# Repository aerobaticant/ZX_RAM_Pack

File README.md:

# ZX RAM Pack
This is my design for a RAM pack for the Sinclair ZX81 computer.
<br>It uses a 62256 SRAM IC to give 32KiB of RAM available to BASIC.

<picture></picture>

## PLD
A 16V8 PLD is used to do the address decoding.

RAM is enabled when A13, A14 or A15 are high ($2000-$FFFF)
<br>RAM area $4000-$7FFF is shadowed at $C000-$FFFF

RAM is read during MREQ or RFSH to allow Hi Res Graphics

ROM shadow is disabled when A15 is high ($8000-$BFFF)
<br>Note: ZX80 has no ROMCS signal so ROM shadow can't be disabled
<br>This means the ZX80 can only be given 16K

ROM is also disabled in address $0004 following reset to allow auto detection
<br>Pull-ups on the data bus generate LD BC,$FFFF instead of LD BC,$7FFF for RAM-CHECK

## Schematic
The Schematic and PCB were created in KiCAD

## STLs
I have also created a 3D printable enclosure based on the design of the original ZX80's 3KB RAM pack.
<br>You may have to rotate the parts to suit your 3D printer.

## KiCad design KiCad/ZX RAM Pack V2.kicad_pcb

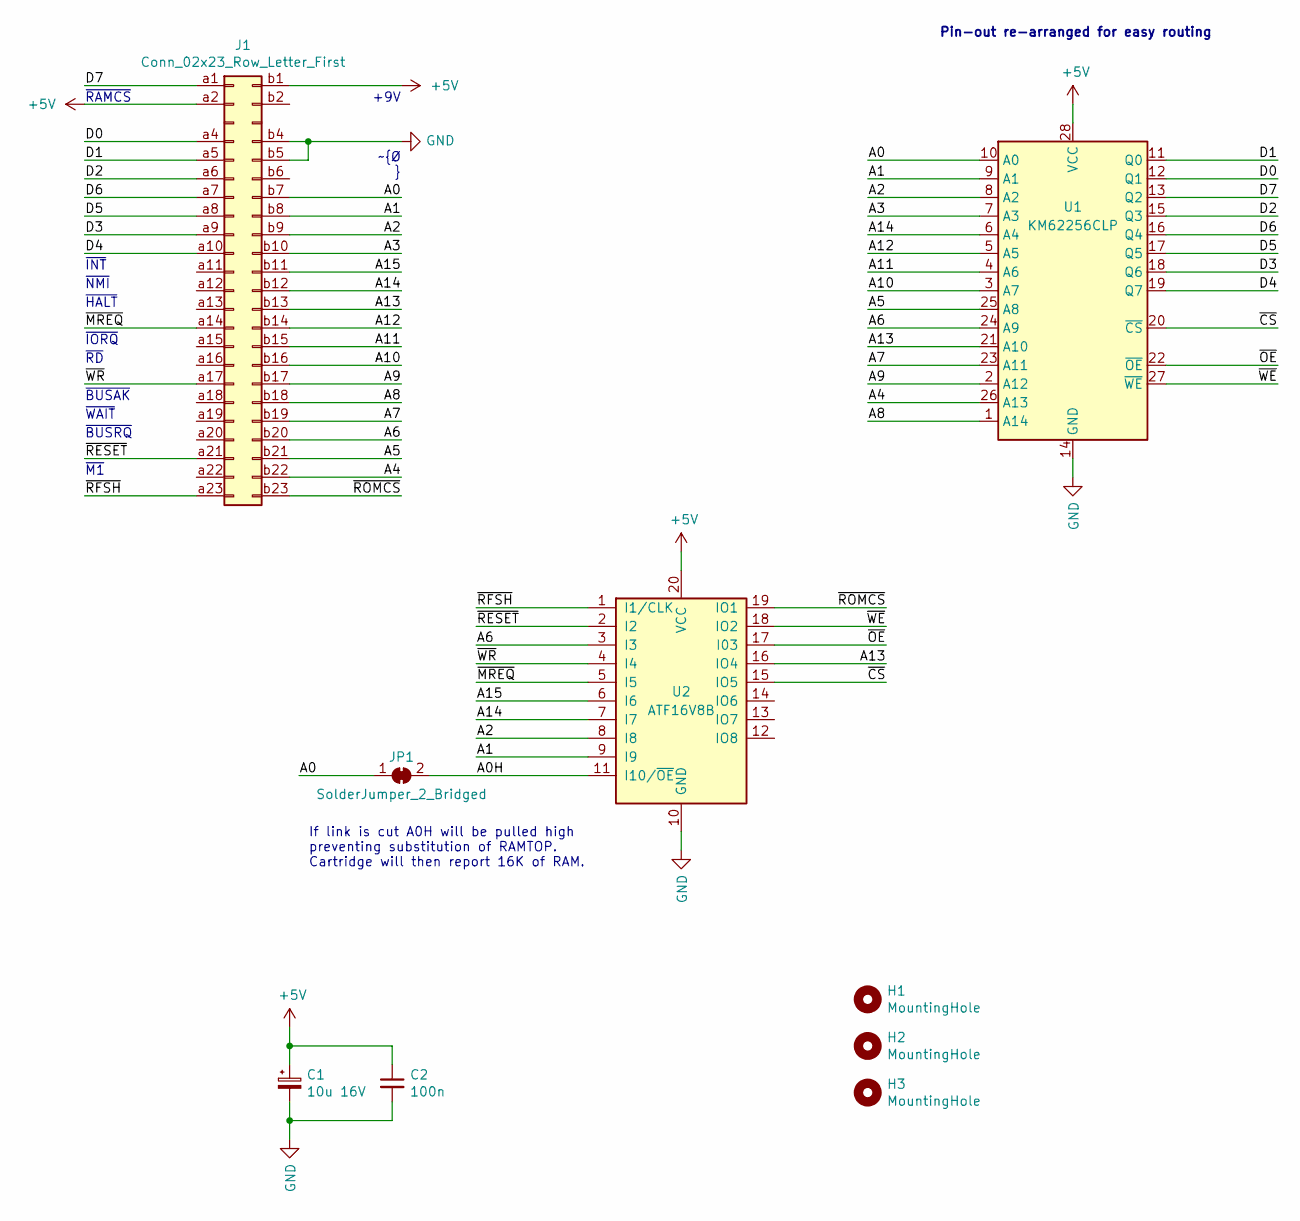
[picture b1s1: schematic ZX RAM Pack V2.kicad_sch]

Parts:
C1: 10u 16V; CP_Radial_D5.0mm_P2.50mm
C2: 100n; C_Disc_D4.3mm_W1.9mm_P5.00mm
H1, H2, H3: MountingHole; MountingHole_3.2mm_M3
J1: Conn_02x23_Row_Letter_First; Connector_ZX80_ZX80_Card_Edge_2x24
JP1: SolderJumper_2_Bridged; SolderJumper-2_P1.3mm_Bridged_RoundedPad1.0x1.5mm
U1: KM62256CLP; DIP-28_W15.24mm_Socket_LongPads
U2: ATF16V8B; DIP-20_W7.62mm_Socket_LongPads

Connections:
+5V: C1.1, C2.1, J1.a2, J1.b1, U1.28 (VCC), U2.20 (VCC)
/A0: J1.b7, JP1.1 (A), U1.10 (A0)
/A0H: JP1.2 (B), U2.11 (I10/~OE)
/A1: J1.b8, U1.9 (A1), U2.9 (I9)
/A2: J1.b9, U1.8 (A2), U2.8 (I8)
/A3: J1.b10, U1.7 (A3)
/A4: J1.b22, U1.26 (A13)
/A5: J1.b21, U1.25 (A8)
/A6: J1.b20, U1.24 (A9), U2.3 (I3)
/A7: J1.b19, U1.23 (A11)
/A8: J1.b18, U1.1 (A14)
/A9: J1.b17, U1.2 (A12)
/A10: J1.b16, U1.3 (A7)
/A11: J1.b15, U1.4 (A6)
/A12: J1.b14, U1.5 (A5)
/A13: J1.b13, U1.21 (A10), U2.16 (IO4)
/A14: J1.b12, U1.6 (A4), U2.7 (I7)
/A15: J1.b11, U2.6 (I6)
/D0: J1.a4, U1.12 (Q1)
/D1: J1.a5, U1.11 (Q0)
/D2: J1.a6, U1.15 (Q3)
/D3: J1.a9, U1.18 (Q6)
/D4: J1.a10, U1.19 (Q7)
/D5: J1.a8, U1.17 (Q5)
/D6: J1.a7, U1.16 (Q4)
/D7: J1.a1, U1.13 (Q2)
/~CS: U1.20 (~CS), U2.15 (IO5)
/~MREQ: J1.a14, U2.5 (I5)
/~OE: U1.22 (~OE), U2.17 (I03)
/~RESET: J1.a21, U2.2 (I2)
/~RFSH: J1.a23, U2.1 (I1/CLK)
/~ROMCS: J1.b23, U2.19 (IO1)
/~WE: U1.27 (~WE), U2.18 (IO2)
/~WR: J1.a17, U2.4 (I4)
GND: C1.2, C2.2, J1.b4, J1.b5, U1.14 (GND), U2.10 (GND)

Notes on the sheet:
+9V
~{IORQ}
~{INT}
If link is cut A0H will be pulled high preventing substitution of RAMTOP. Cartridge will then report 16K of RAM.
~{BUSRQ}
~{NMI}
Pin-out re-arranged for easy routing
~{RAMCS}
~{WAIT}
~{M1}
~{Ø }
~{HALT}
~{BUSAK}
~{RD}

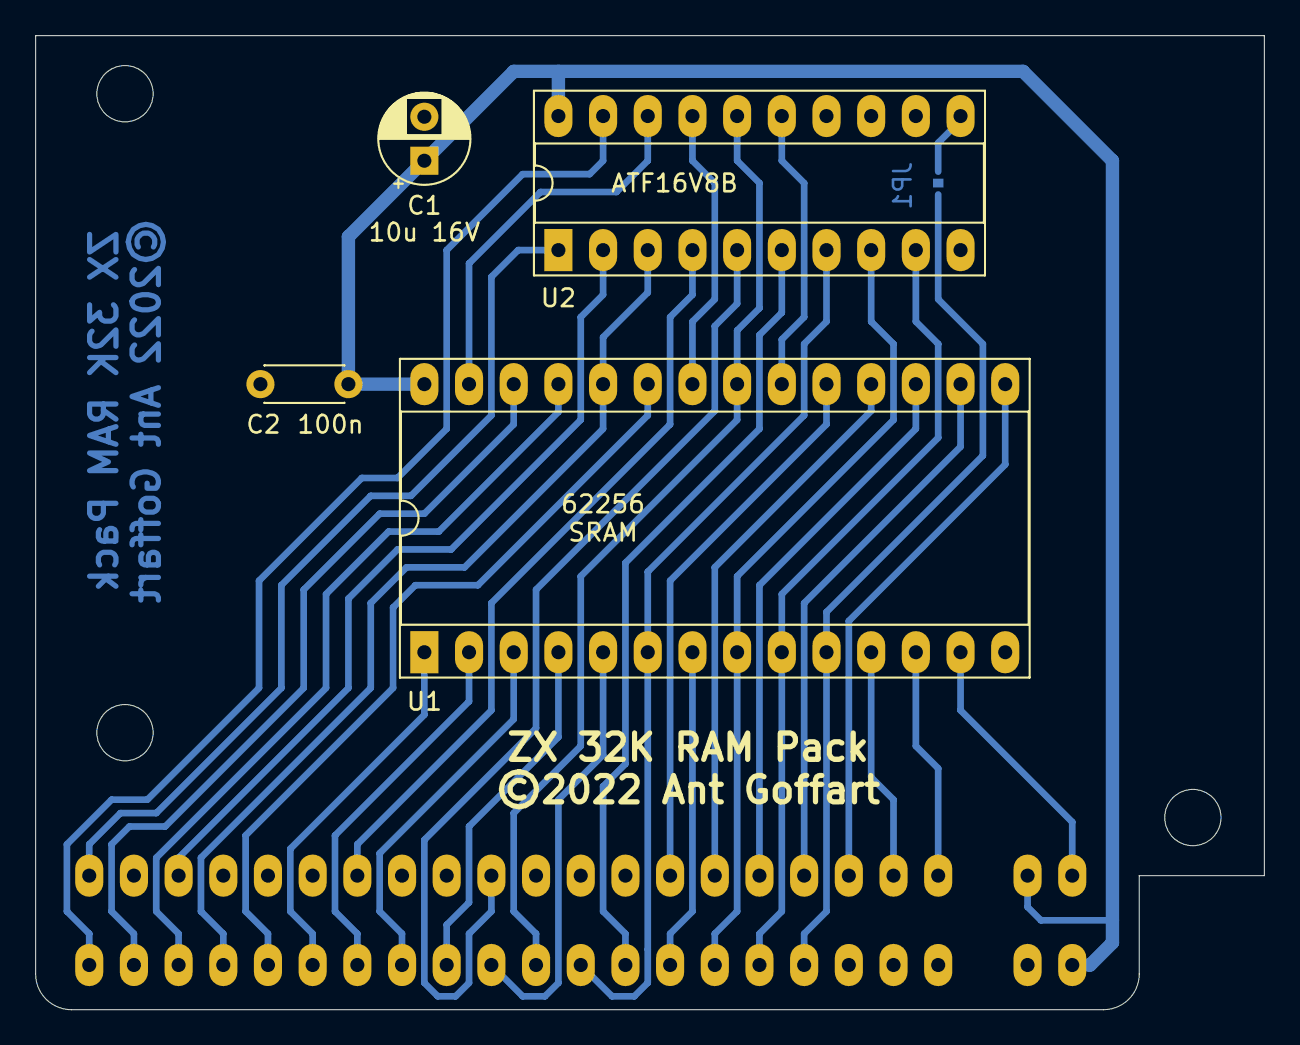
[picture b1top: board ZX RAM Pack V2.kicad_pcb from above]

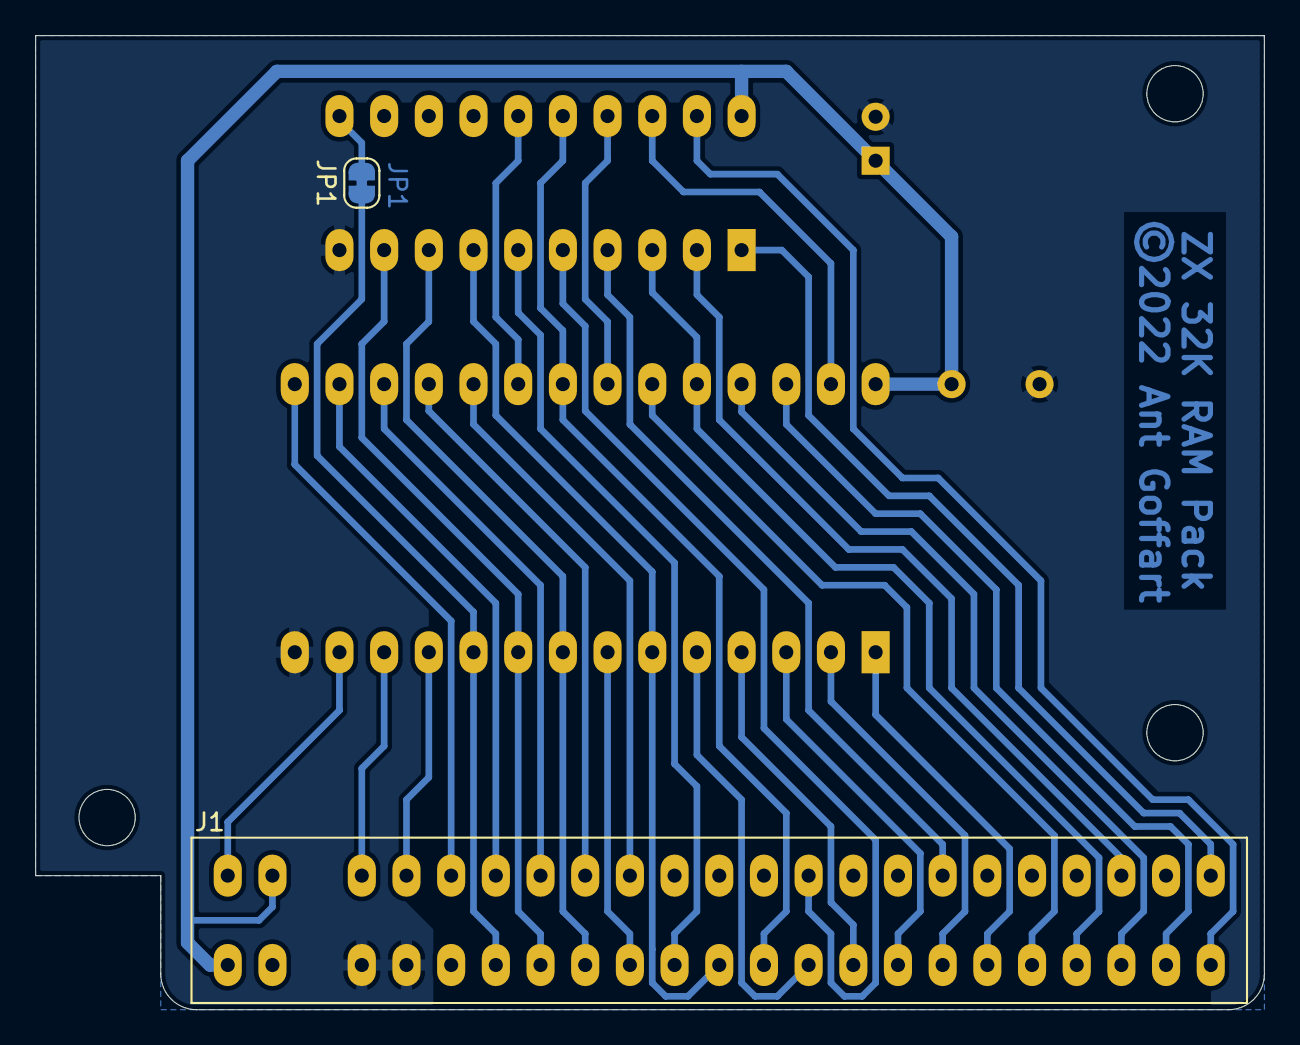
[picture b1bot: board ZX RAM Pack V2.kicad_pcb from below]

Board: 2 copper layers, 69.8 x 55.4 mm, 9 parts (2 on the bottom side), 35 nets.

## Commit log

2023-12-12 Add initial project files
2023-12-12 Add KiCad Design
2023-12-12 Add picture to README.md

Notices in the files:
KiCad/ZX RAM Pack V2.kicad_pcb:
©2022 Ant Goffart
